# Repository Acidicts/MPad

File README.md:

# M-Pad
### Media-Pad (Media-Hackpad)

A Hackpad but this time made for media with 3 dedicated keys for Back, Play/Pause, and Skip along with volume controls via a rotary encoder.
Powered by kmk on circuitpython

<div>

    <div style="display: inline-flex; justify-content: space-between; margin-top: 10px;">

    </div>
</div>

### Case
- The lid is [here](./case/Lid.step)
- The case is [here](./case/Case.step)
- The Custom encoder knob is [here](./case/Encoder_Knob.step)
- The detachable stand that mounts in the two square holes in the back is [here](./case/Detachable_Stand.step)
- Fusion 360 file is [here](https://a360.co/4gD1b6e)

### Key Mappings
---
<div style="display: inline-flex; justify-content: space-between;">
    <div style="border-right: 1px solid #888; padding-right: 10px; margin-right: 10px;">
        <strong>Key Switches</strong>
        <table>
            <thead>
                <tr>
                    <th>Function</th>
                    <th>Key</th>
                </tr>
            </thead>
            <tbody>
                <tr><td>Back</td><td>KC.WBAK</td></tr>
                <tr><td>Play/Pause</td><td>KC.MPLY</td></tr>
                <tr><td>Skip</td><td>KC.WFWD</td></tr>
            </tbody>
        </table>
    </div>
    <div>
        <strong>Encoder Mapping</strong>
        <table>
            <thead>
                <tr>
                    <th>Function</th>
                    <th>Key</th>
                </tr>
            </thead>
            <tbody>
                <tr><td>Volume Down</td><td>KC.VOLD</td></tr>
                <tr><td>Volume Up</td><td>KC.VOLU</td></tr>
                <tr><td>Mute</td><td>KC.MUTE</td></tr>
            </tbody>
        </table>
    </div>
</div>

### BOM
---
- [BOM](./assets/BOM.csv)
- [LCSC Component BOM](./assets/LCSC_BOM.csv)

### Getting Started
1. Download the latest release of circuitpython from [here](https://downloads.circuitpython.org/bin/seeeduino_xiao_rp2040/en_GB/adafruit-circuitpython-seeeduino_xiao_rp2040-en_GB-10.3.0.uf2)
2. whilst powering the Seeed Studio XIAO RP2040, hold down the boot button and plug it into your computer. The board should show up as a USB drive called `RPI-RP2`.
3. Drag and drop the downloaded UF2 file onto the `RPI-RP2` drive. The board will reboot and show up as a USB drive called `CIRCUITPY`.
4. drag and drop the contents of the [`firmware`](./firmware) folder onto the `CIRCUITPY` drive.
5. Restart the board and it should now be ready to use.

~ Note It is configured for getting stock prices edit the firmware to do as you see fit
~ It uses [main.py](main.py) on the host to communicate over serial

### Soldering Guide
~ Note the capacitors and resistors on the pcb are optional, as they are for decoupling and filtering
1. Use flux on the surface of the pads
2. Place LEDS reverse mounted
3. Solder them
4. Position the diodes with the side with the line facing the same way as in the silk screen
5. Solder them on
6. Solder the ssd1306 oled display (128x32) so the long legs for it stick down
7. Place the m3 screw in the hole then put oled display over top and solder it on
8. Solder on the Xiao
9. solder on the keycaps
10. If you don't have the resistor, bridge the gap using solder
11. push in the EC11E rotary encoder and solder in
12. You're done!!!

### Want to edit the code
1. Hold the middle switch whilst plugging in the board to your computer. The board should show up as a USB drive called `CIRCUITPY`.
2. Edit it as if it is a normal drive. 

### Demo video

<video src="https://github.com/user-attachments/assets/15901fed-9ee6-4e93-8e1c-391db2670cf7" controls="controls" style="max-width: 100%;" title="Demo Video.mp4">
</video>

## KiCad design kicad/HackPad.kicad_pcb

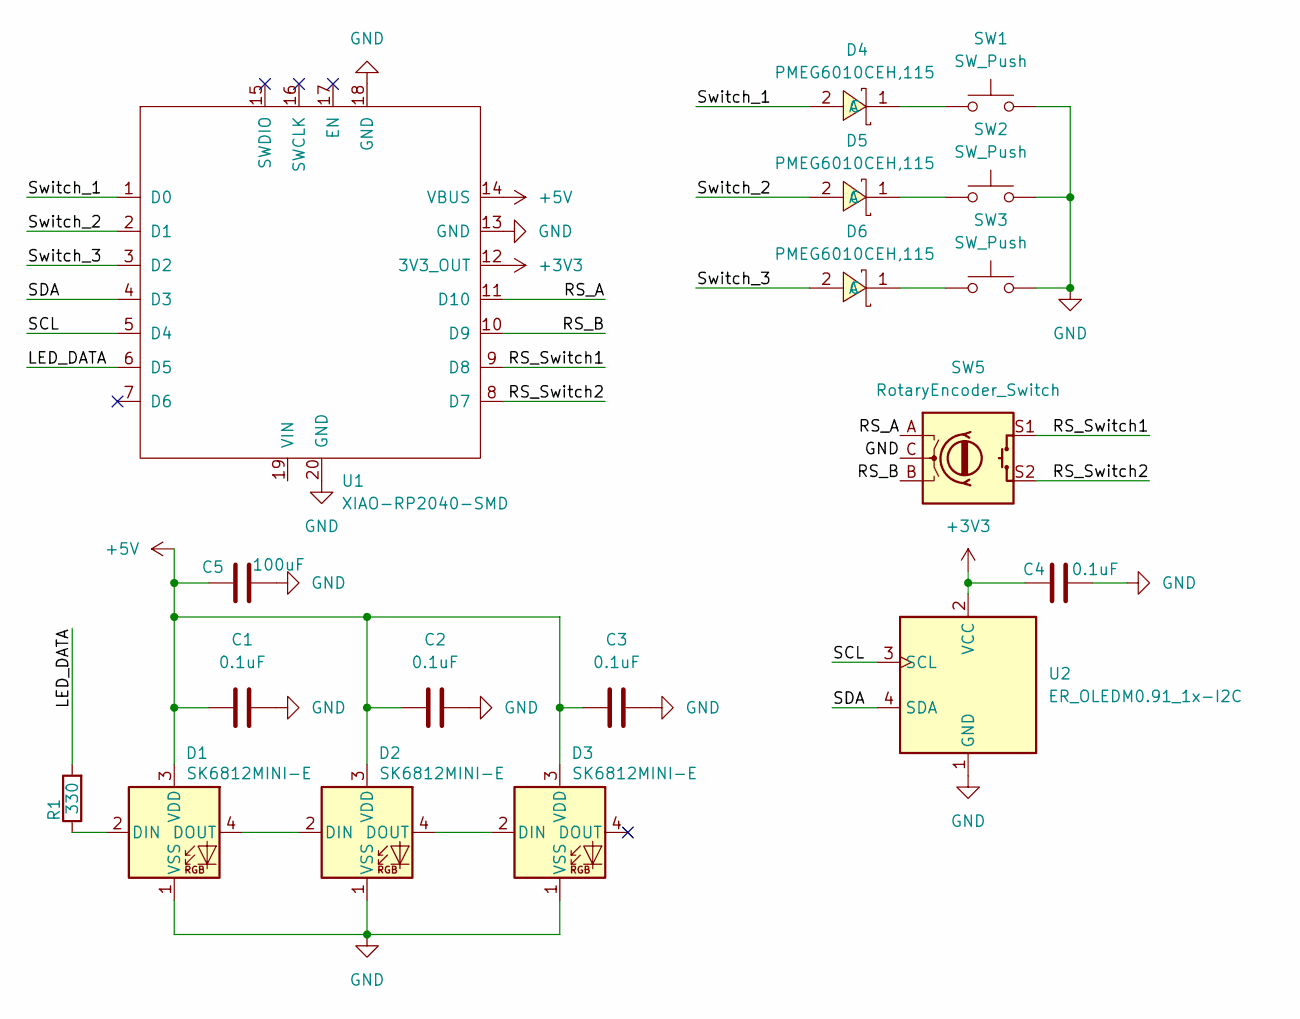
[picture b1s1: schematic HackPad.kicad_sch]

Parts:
C1, C2, C3, C4: 0.1uF; C_0603_1608Metric; LCSC C1591
C5: 100uF; C_1206_3216Metric; LCSC C15008
D1, D2, D3: SK6812MINI-E; LED_SK6812MINI-E_3.2x2.8mm_P1.5mm_ReverseMount
D4, D5, D6: PMEG6010CEH,115; SOD-123FL_L2.7-W1.8-LS3.8-RD; MPN PMEG6010CEH,115; LCSC Part C110797
R1: 330; C_0603_1608Metric; LCSC C105881
SW1, SW2, SW3: SW_Push; SW_Cherry_MX_1.00u_PCB
SW5: RotaryEncoder_Switch; RotaryEncoder_Alps_EC11E-Switch_Vertical_H20mm
U1: XIAO-RP2040-SMD
U2: ER_OLEDM0.91_1x-I2C

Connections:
+3V3: C4.1, U1.12 (3V3_OUT), U2.2 (VCC)
+5V: C1.1, C2.1, C3.1, C5.1, D1.3 (VDD), D2.3 (VDD), D3.3 (VDD), U1.14 (VBUS)
/LED_DATA: R1.2, U1.6 (D5)
/RS_A: SW5.A, U1.11 (D10)
/RS_B: SW5.B, U1.10 (D9)
/RS_Switch1: SW5.S1, U1.9 (D8)
/RS_Switch2: SW5.S2, U1.8 (D7)
/SCL: U1.5 (D4), U2.3 (SCL)
/SDA: U1.4 (D3), U2.4 (SDA)
/Switch_1: D4.2 (A), U1.1 (D0)
/Switch_2: D5.2 (A), U1.2 (D1)
/Switch_3: D6.2 (A), U1.3 (D2)
GND: C1.2, C2.2, C3.2, C4.2, C5.2, D1.1 (VSS), D2.1 (VSS), D3.1 (VSS), SW1.2, SW2.2, SW3.2, SW5.C, SW5.MP, U1.13 (GND), U1.18 (GND), U1.20 (GND), U2.1 (GND)
unnamed: D1.2 (DIN), R1.1
unnamed: D1.4 (DOUT), D2.2 (DIN)
unnamed: D2.4 (DOUT), D3.2 (DIN)
unnamed: D4.1 (C), SW1.1
unnamed: D5.1 (C), SW2.1
unnamed: D6.1 (C), SW3.1

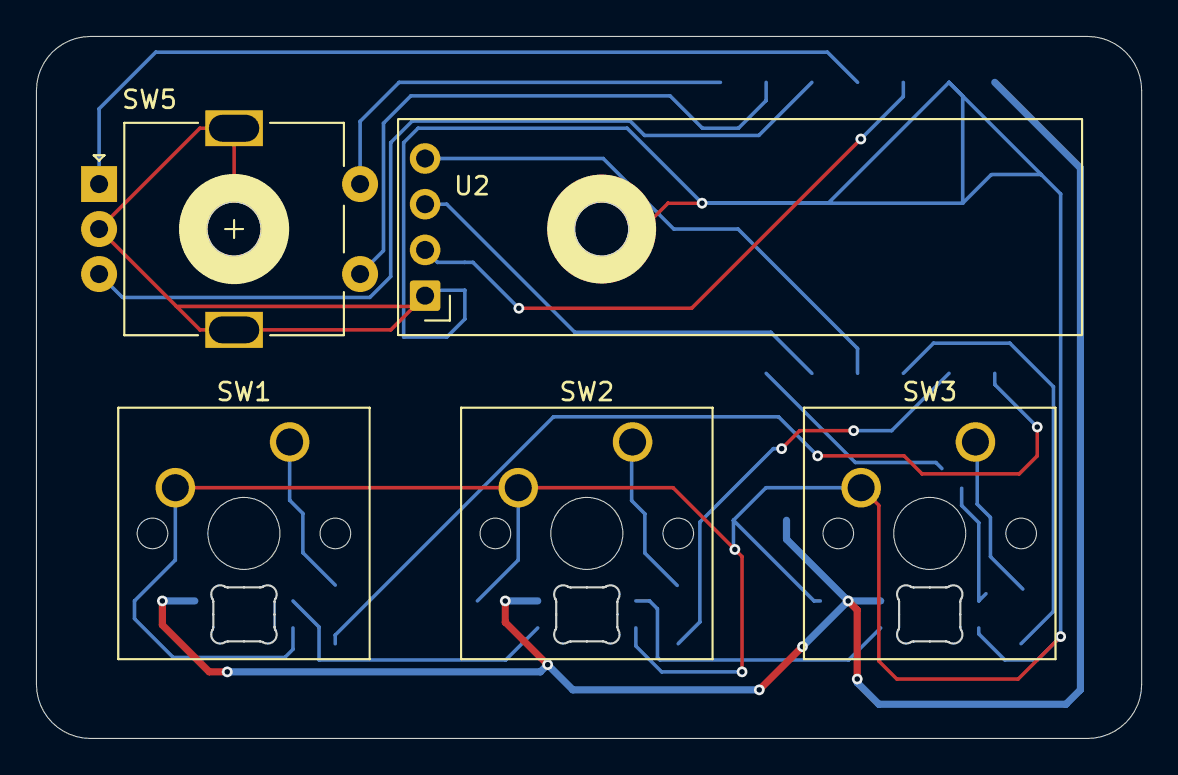
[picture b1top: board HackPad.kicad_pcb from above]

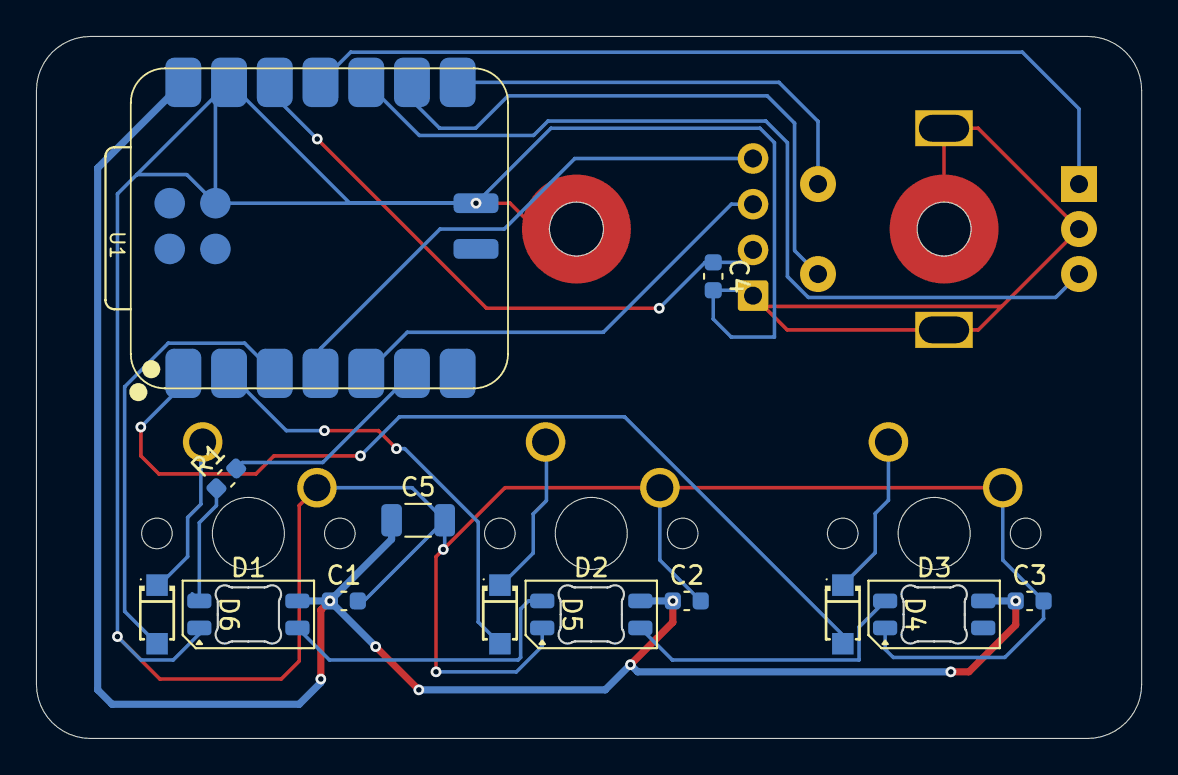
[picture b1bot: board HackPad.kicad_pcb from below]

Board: 2 copper layers, 61.4 x 39.0 mm, 18 parts (13 on the bottom side), 19 nets.

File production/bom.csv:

Designator,Footprint,Quantity,Value,LCSC Part #
"C1, C2, C3, C4",0603,4,0.1uF,C1591
C5,1206,1,100uF,C15008
"D1, D2, D3",LED_SK6812MINI-E_3.2x2.8mm_P1.5mm_ReverseMount,3,SK6812MINI-E,
"D4, D5, D6",SOD-123FL_L2.7-W1.8-LS3.8-RD,3,"PMEG6010CEH,115",C110797
R1,0603,1,330,C105881
"SW1, SW2, SW3",SW_Cherry_MX_1.00u_PCB,3,SW_Push,
SW5,RotaryEncoder_Alps_EC11E-Switch_Vertical_H20mm,1,RotaryEncoder_Switch,
U1,XIAO-RP2040-SMD,1,XIAO-RP2040-SMD,
U2,ER_OLEDM0.91_1x-I2C,1,ER_OLEDM0.91_1x-I2C,

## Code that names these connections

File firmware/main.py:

# You import all the IOs of your board
import board

# These are imports from the kmk library
from kmk.kmk_keyboard import KMKKeyboard
from kmk.scanners.keypad import KeysScanner
from kmk.extensions.RGB import RGB, AnimationModes
from kmk.extensions.media_keys import MediaKeys
from kmk.modules.macros import Macros
from kmk.modules.encoder import EncoderHandler
from kmk.keys import KC

# Pin definitions based on your schematic
ROTA = board.D10         # RS_A
ROTB = board.D9          # RS_B
RS_Switch1 = board.D8    # Push Button Pin 1
RS_Switch2 = board.D7    # Push Button Pin 2

NEOPIXEL = board.D5

# This is the main instance of your keyboard
keyboard = KMKKeyboard()

# Add the macro extension
macros = Macros()
keyboard.modules.append(macros)

# Define your matrix pins here (Switch_1, Switch_2, Switch_3)
PINS = [board.D0, board.D1, board.D2]

# RGB LEDs settings
rgb_ext = RGB( 
    pixel_pin = NEOPIXEL,
    num_pixels = 3,
    hue_default = 100,
    sat_default = 255,
    val_default = 15,
    val_limit = 25,
    animation_speed = 1,
    animation_mode = AnimationModes.RAINBOW,
    refresh_rate = 30,
)
keyboard.extensions.append(rgb_ext)
keyboard.extensions.append(MediaKeys())

# Tell kmk we are not using a key matrix for the switches
keyboard.matrix = KeysScanner(
    pins = PINS,
    value_when_pressed = False,
)

# Encoder settings using RS_Switch1 (D8) and RS_Switch2 (D7) from your schematic
encoder_handler = EncoderHandler()
keyboard.modules.append(encoder_handler)
encoder_handler.pins = ((board.D8, board.D7, None, False),)
encoder_handler.map = (((KC.VOLD, KC.VOLU, KC.MUTE),),)

# Here you define the buttons corresponding to the pins
keyboard.keymap = [
    [KC.MPRV, KC.MPLY, KC.MNXT]
]

# Start kmk!
if __name__ == '__main__':
    keyboard.go()
